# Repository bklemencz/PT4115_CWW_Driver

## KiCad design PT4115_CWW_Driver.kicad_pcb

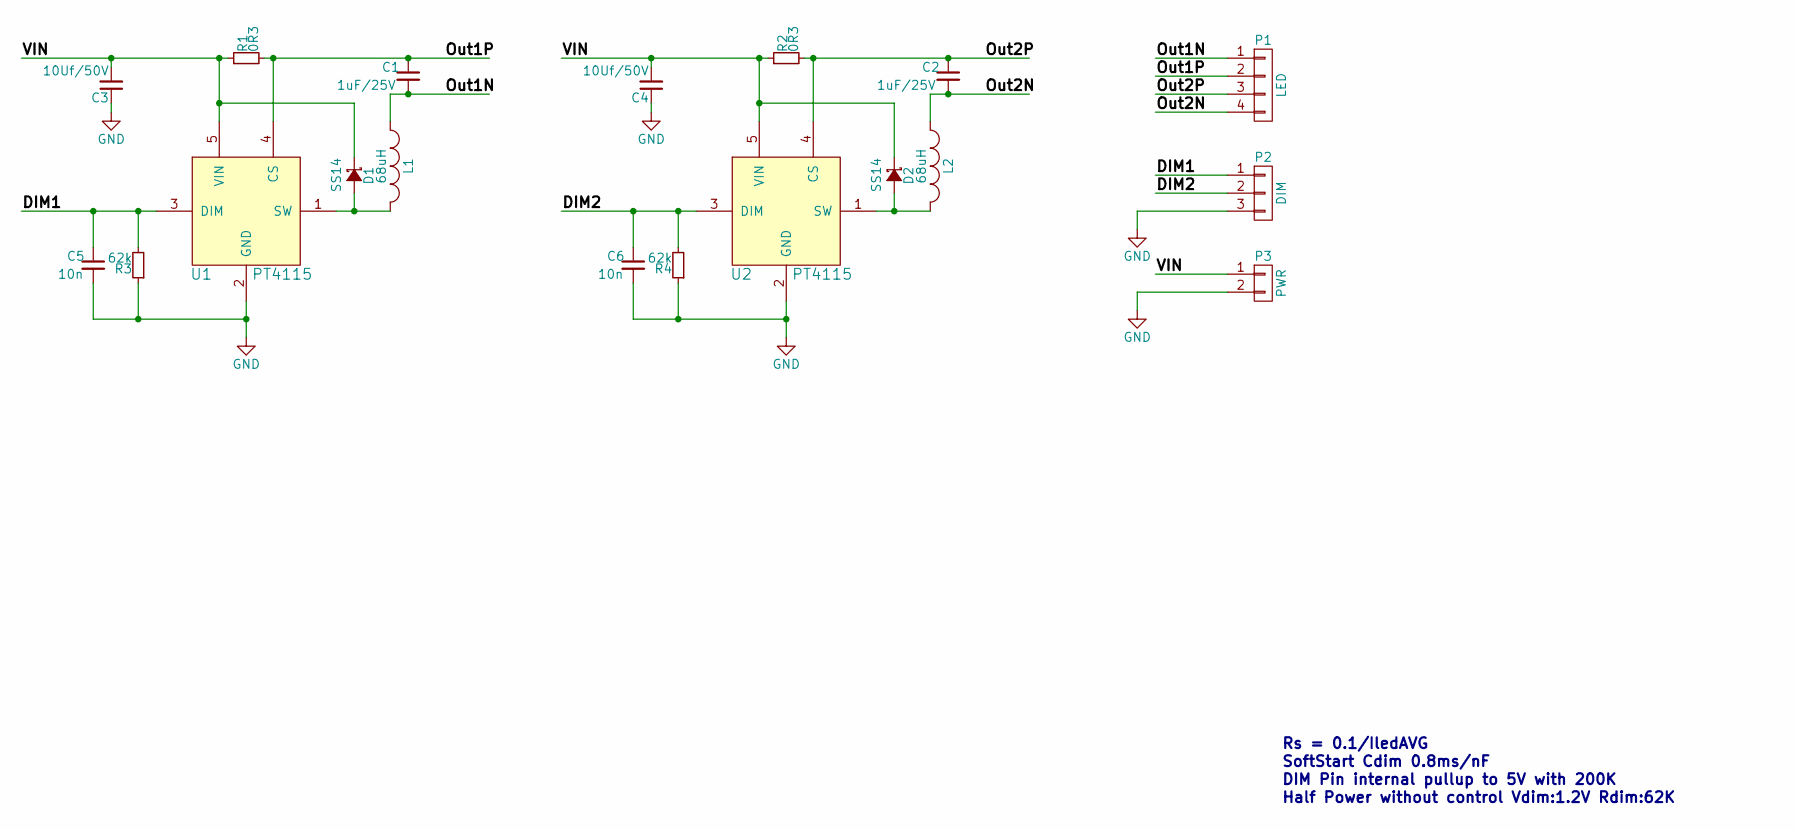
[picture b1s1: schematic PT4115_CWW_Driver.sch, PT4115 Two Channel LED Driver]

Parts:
C1, C2: 1uF/25V; C_0805
C3, C4: 10Uf/50V; C_1206
C5, C6: 10n; C_0805
D1, D2: SS14; D_SMA
L1, L2: 68uH; IND_SMD_CD54
P1: LED; Pin_Header_Straight_1x04_Pitch2.54mm
P2: DIM; Pin_Header_Straight_1x03_Pitch2.54mm
P3: PWR; Pin_Header_Straight_1x02_Pitch2.54mm
R1, R2: 0R3; R_0805
R3, R4: 62k; R_0805
U1, U2: PT4115; SOT89-5_Housing

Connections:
/DIM1: C5.1, P2.1, R3.2, U1.3 (DIM)
/DIM2: C6.1, P2.2, R4.2, U2.3 (DIM)
/Out1N: C1.2, L1.1, P1.1
/Out1P: C1.1, P1.2, R1.2, U1.4 (CS)
/Out2N: C2.2, L2.1, P1.4
/Out2P: C2.1, P1.3, R2.2, U2.4 (CS)
/VIN: C3.2, C4.2, D1.1 (K), D2.1 (K), P3.1, R1.1, R2.1, U1.5 (VIN), U2.5 (VIN)
GND: C3.1, C4.1, C5.2, C6.2, P2.3, P3.2, R3.1, R4.1, U1.2 (GND), U2.2 (GND)
unnamed: D1.2 (A), L1.2, U1.1 (SW)
unnamed: D2.2 (A), L2.2, U2.1 (SW)

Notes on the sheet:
Rs = 0.1/IledAVG
SoftStart Cdim 0.8ms/nF
DIM Pin internal pullup to 5V with 200K
Half Power without control Vdim:1.2V Rdim:62K

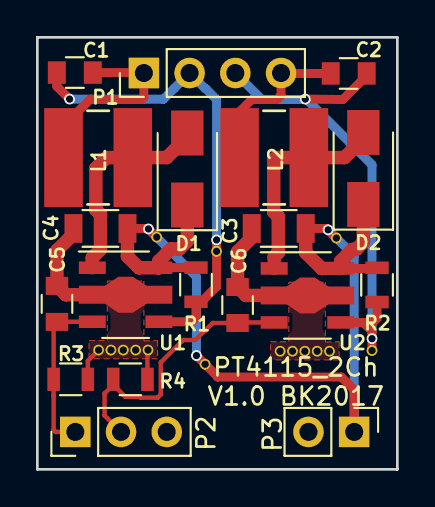
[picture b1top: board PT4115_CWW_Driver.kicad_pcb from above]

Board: 2 copper layers, 20.0 x 24.0 mm, 19 parts (0 on the bottom side), 10 nets.

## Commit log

2017-09-05 :lollipop: Added .gitattributes & .gitignore files
2017-09-05 initial
2017-09-05 Gerber Output
2017-09-19 PCB Outpu Changes
